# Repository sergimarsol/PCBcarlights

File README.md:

# PCB Car Lights

## Overview

PCB Car Lights is a project focused on the design and implementation of a printed circuit board (PCB) for controlling the lights of a car. This project provides the schematic and layout for the electronic components needed to efficiently manage car lighting systems.

## Table of Contents

1. [Introduction](#introduction)
2. [Getting Started](#getting-started)
3. [Schematic and Layout](#schematic-and-layout)
4. [Components](#components)
5. [Presentation](#presentation)
6. [Contributing](#contributing)

## Introduction

Modern cars rely on sophisticated lighting systems for safety and aesthetics. The PCB Car Lights project aims to streamline the control of car lights, providing a compact and efficient solution through a custom-designed PCB.

## Getting Started

To get started with the PCB Car Lights project, follow these steps:

1. **Clone the Repository:**
   ```bash
   git clone https://github.com/your-username/PCBcarlights.git
   ```

2. **Explore the Documentation:**
   Review the documentation files, including the README, to understand the project structure and requirements.

3. **Set Up Development Environment:**
   Ensure you have the necessary tools and software installed for PCB design. Refer to the documentation for specific requirements.

4. **Modify Design:**
   Customize the PCB design according to your car's lighting specifications, making any necessary adjustments to the schematic and layout.

5. **Testing:**
   Before manufacturing the PCB, simulate and test the design using appropriate tools to ensure functionality.

## Schematic and Layout

The schematic diagram provides an overview of the electronic components and their connections and the PCB layout file defines the physical arrangement of components on the board. Open both files using [Kicad] to view the schematic and the layout of the implemented PCB. Screenshots of both files and of the block diagram are also provided:

- [View Block diagram](./imgs/block_diagram.PNG)
- [View Schematic](./imgs/SCH_image.PNG)
- [View PCB](./imgs/PCB_image.PNG)

All of these can be observed in the provided presentation.

## Components

To view the components refer to the .xlsx file containing them along with their budget.

- [View components and budget](./Components_budget.xlsx)

The most relevant components can be found in the provided presentation

## Presentation

Included in this repository is a PDF presentation (`PCBcarlights_Presentation.pdf`) that provides a comprehensive overview of the project. The presentation covers background, design methodology, key features, and potential applications of the PCB Car Lights project.

## Contributing

If you have any questions or feedback, feel free to reach out to me.

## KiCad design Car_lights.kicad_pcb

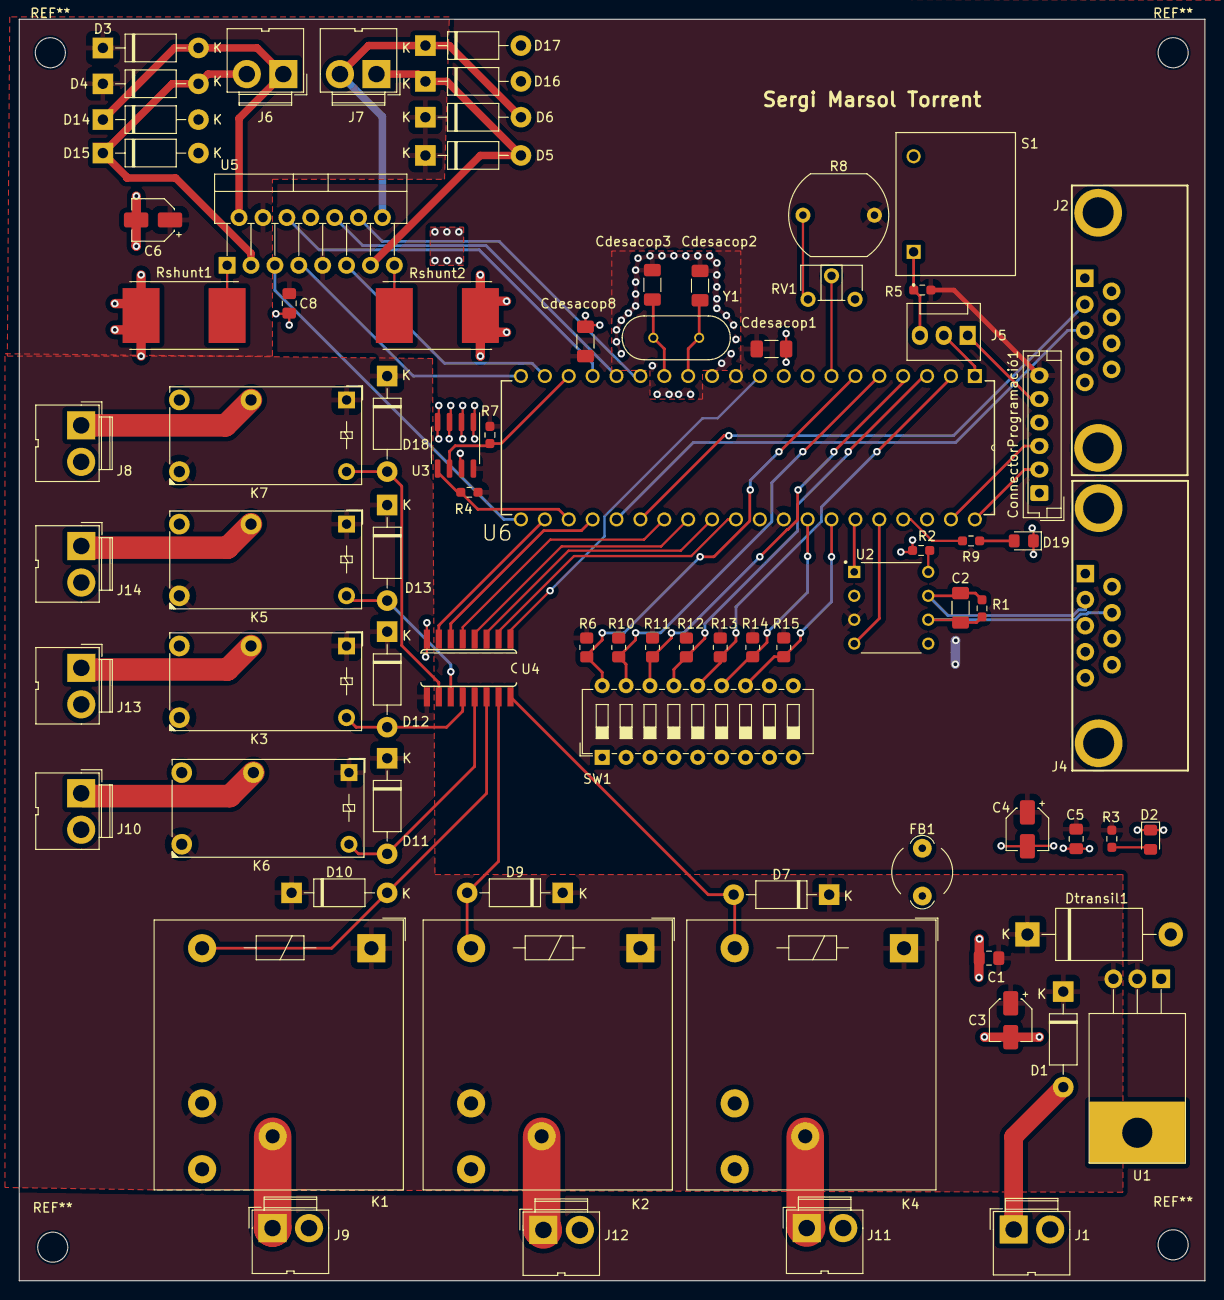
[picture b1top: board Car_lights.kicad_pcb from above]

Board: 2 copper layers, 126.1 x 134.1 mm, 80 parts (1 on the bottom side), 66 nets.

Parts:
C1, C5, C8: 100n; C_0805_2012Metric_Pad1.18x1.45mm_HandSolder
C2: 100p; C_1206_3216Metric_Pad1.33x1.80mm_HandSolder
C3, C4: 1u; CP_Elec_4x5.4
C6: 220n; CP_Elec_4x5.4
C7: 100n; C_1206_3216Metric_Pad1.33x1.80mm_HandSolder
Cdesacop1, Cdesacop8: 100n; C_1206_3216Metric_Pad1.33x1.80mm_HandSolder
Cdesacop2, Cdesacop3: 100p; C_1206_3216Metric_Pad1.33x1.80mm_HandSolder
ConnectorProgramació1: Conn_01x06; JST_EH_B6B-EH-A_1x06_P2.50mm_Vertical
D1, D7, D9, D10, D11, D12, D13, D18: 1N4002; D_DO-41_SOD81_P10.16mm_Horizontal
D2, D19: LED; LED_0805_2012Metric_Pad1.15x1.40mm_HandSolder
D3, D4, D5, D6, D14, D15, D16, D17: 1N4007; D_DO-41_SOD81_P10.16mm_Horizontal
Dtransil1: 1.5KExxA; D_DO-201AE_P15.24mm_Horizontal
FB1: FerriteBead; LairdTech_28C0236-0JW-10
J1: Conn_bat; JWT_A3963_1x02_P3.96mm_Vertical
J2: DB9_ConnectorUSART; DB9
J4: DB9_ConnectorCAN; DB9
J5: Conn_01x03; FanPinHeader_1x03_P2.54mm_Vertical
J6: Conn_Motor1; JWT_A3963_1x02_P3.96mm_Vertical
J7: Conn_Motor2; JWT_A3963_1x02_P3.96mm_Vertical
J8: Conn_I.E; JWT_A3963_1x02_P3.96mm_Vertical
J9: Conn_Fre; JWT_A3963_1x02_P3.96mm_Vertical
J10: Conn_Cruce; JWT_A3963_1x02_P3.96mm_Vertical
J11: Conn_Largas; JWT_A3963_1x02_P3.96mm_Vertical
J12: Conn_Antiniebla; JWT_A3963_1x02_P3.96mm_Vertical
J13: Conn_Posicio; JWT_A3963_1x02_P3.96mm_Vertical
J14: Conn_I.D; JWT_A3963_1x02_P3.96mm_Vertical
K1, K2, K4: G5LE-14-CF_DC24; Relay_SPDT_Finder_40.11
K3, K5, K6, K7: G5NB-1A-DC24; Relay_SPDT_Finder_32.21-x000
R1: 100; R_0603_1608Metric_Pad0.98x0.95mm_HandSolder
R2, R3, R5, R9: 1k; R_0603_1608Metric_Pad0.98x0.95mm_HandSolder
R4, R7: 4.7k; R_0603_1608Metric_Pad0.98x0.95mm_HandSolder
R6, R10, R11, R12, R13, R14, R15: 22k; R_0805_2012Metric_Pad1.20x1.40mm_HandSolder
R8: LDR03; R_LDR_10x8.5mm_P7.6mm_Vertical
RV1: R_Potentiometer; Potentiometer_ACP_CA6-H2,5_Horizontal
Rshunt1, Rshunt2: 250; R_Shunt_Vishay_WSR2_WSR3
S1: A3AT-91L1-00R; SW_A3AT-91L1-00R
SW1: SW_DIP_x09; SW_DIP_SPSTx09_Slide_6.7x24.42mm_W7.62mm_P2.54mm_LowProfile
U1: LM1117S-5.0; TO-220-3_Horizontal_TabDown (P2)
U2: MCP2551-I/P; DIP787W46P254L927H533Q8
U3: 24C02C/P; SOIC-8_3.9x4.9mm_P1.27mm
U4: ULN2003; SO16
U5: L298N; TO-220-15_P2.54x2.54mm_StaggerOdd_Lead4.58mm_Vertical
U6: PIC18F458-I/P; DIP254P1524X483-40
Y1: HC-49; XTAL_HC49P488W43L1150T466H350

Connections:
/+motor1: D3.2 (A), D14.1 (K), J6.1, U5.2 (OUT1)
/+motor2: D5.2 (A), D16.1 (K), J7.1, U5.13 (OUT3)
/-motor1: D4.2 (A), D15.1 (K), J6.2, U5.3 (OUT2)
/-motor2: D6.2 (A), D17.1 (K), J7.2, U5.14 (OUT4)
/CAN+: C2.1, J4.2, R1.1, U2.7 (CANH)
/CAN-: C2.2, J4.7, R1.2, U2.6 (CANL)
/CANRX: U2.4 (RXD), U6.36 (RB3/CANRX)
/CANTX: U2.1 (TXD), U6.35 (RB2/CANTX/INT2)
/Corriente3A_1: J10.1, K6.11
/Corriente3A_2: J13.1, K3.11
/Corriente3A_3: J14.1, K5.11
/Corriente3A_4: J8.1, K7.11
/Corriente8A_1: J11.1, K4.11
/Corriente8A_2: J12.1, K2.11
/Corriente8A_3: J9.1, K1.11
/MCLR: J5.2, U6.1 (~MCLR/VPP)
/PGC: ConnectorProgramació1.3, U6.39 (RB6/PGC)
/PGD: ConnectorProgramació1.2, U6.40 (RB7/PGD)
/PROG.MCLR: ConnectorProgramació1.5, J5.1
/Reset: J5.3, R5.2, S1.1
/led programació: D19.2 (A), R9.1
ADC: RV1.2, U6.7 (RA5/AN4/~SS/LVDIN)
CLK0: Cdesacop3.2, U6.14 (OSC2/CLKO/RA6), Y1.1
CLK1: Cdesacop2.1, U6.13 (OSC1/CLKI), Y1.2 (CRYSTAL_2)
ENA: U5.6 (EnA), U6.17 (RC2/CCP1)
ENB: U5.11 (EnB), U6.19 (RD0/PSP0/C1IN+)
GND: C4.2, C5.2, C7.2, C8.1, Cdesacop1.2, Cdesacop2.2, Cdesacop3.1, Cdesacop8.2, ConnectorProgramació1.1, D2.1 (K), D19.1 (K), FB1.2, J2.5, J4.3, R2.1, RV1.3, S1.2, SW1.1, SW1.2, SW1.3, SW1.4, SW1.5, SW1.6, SW1.7, U2.2 (VSS), U3.1 (E0), U3.2 (E1), U3.3 (E2), U3.4 (VSS), U3.7 (~WC), U4.8 (GND), U5.8 (GND), U6.12 (VSS_2), U6.31 (VSS)
GNDPWR: C1.2, C3.2, C6.2, D14.2 (A), D15.2 (A), D16.2 (A), D17.2 (A), Dtransil1.2 (A2), FB1.1, J1.2, J8.2, J9.2, J10.2, J11.2, J12.2, J13.2, J14.2, K1.14, K2.14, K3.14, K4.14, K5.14, K6.14, K7.14, Rshunt1.2, Rshunt2.2, U1.1 (GND)
I1: U4.1 (I1), U6.10 (RE2/AN7/~CS/C2OUT)
I2: U4.2 (I2), U6.30 (RD7/PSP7/P1D)
I3: U4.3 (I3), U6.29 (RD6/PSP6/P1C)
I4: U4.4 (I4), U6.28 (RD5/PSP5/P1B)
I5: U4.5 (I5), U6.27 (RD4/PSP4/ECCP1/P1A)
I6: U4.6 (I6), U6.24 (RC5/SDO)
I7: U4.7 (I7), U6.22 (RD3/PSP3/C2IN-)
IN1: U5.5 (IN1), U6.21 (RD2/PSP2/C2IN+)
IN2: U5.7 (IN2), U6.20 (RD1/PSP1/C1IN-)
IN3: U5.10 (IN3), U6.16 (RC1/T1OSI)
IN4: U5.12 (IN4), U6.15 (RC0/T1OSO/T1CK1)
unnamed: D2.2 (A), R3.2
unnamed: R8.1, RV1.1
unnamed: R2.2, U2.8 (RS)
unnamed: Rshunt1.1, U5.1 (SENSE_A)
unnamed: Rshunt2.1, U5.15 (SENSE_B)
unnamed: R9.2, U6.37 (RB4)
R1: D7.2 (A), K4.A2, U4.16 (O1)
R2: D9.2 (A), K2.A2, U4.15 (O2)
R3: D10.2 (A), K1.A2, U4.14 (O3)
R4: D11.2 (A), K6.A2, U4.13 (O4)
R5: D12.2 (A), K3.A2, U4.12 (O5)
R6: D13.2 (A), K5.A2, U4.11 (O6)
R7: D18.2 (A), K7.A2, U4.10 (O7)
RA0: R6.2, SW1.18, U6.6 (RA4/T0CKI)
RA1: R10.2, SW1.17, U6.5 (RA3/AN3/VREF+)
RA2: R11.2, SW1.16, U6.4 (RA2/AN2/VREF-)
RA3: R12.2, SW1.15, U6.3 (RA1/AN1)
RA4: R13.2, SW1.14, U6.2 (RA0/AN0/CVREF)
RB0: R15.2, SW1.12, U6.34 (RB1/INT1)
RB1: R14.2, SW1.13, U6.33 (RB0/INT0)
RX: J2.2, U6.26 (RC7/RX/DT)
SCL: R7.2, U3.6 (SCL), U6.18 (RC3/SCK/SCL)
SDA: R4.2, U3.5 (SDA), U6.23 (RC4/SDI/SDA)
TX: J2.3, U6.25 (RC6/TX/CK)
VBAT: D1.2 (A), J1.1
VBAT-PROT: C1.1, C3.1, C6.1, D1.1 (K), D3.1 (K), D4.1 (K), D5.1 (K), D6.1 (K), D7.1 (K), D9.1 (K), D10.1 (K), D11.1 (K), D12.1 (K), D13.1 (K), D18.1 (K), Dtransil1.1 (A1), K1.12, K1.A1, K2.12, K2.A1, K3.12, K3.A1, K4.A1, K5.12, K5.A1, K6.12, K6.A1, K7.12, K7.A1, U1.3 (VI), U4.9 (COM), U5.4 (Vs)
VCC: C4.1, C5.1, C7.1, C8.2, Cdesacop1.1, Cdesacop8.1, ConnectorProgramació1.6, R3.1, R4.1, R5.1, R6.1, R7.1, R8.2, R10.1, R11.1, R12.1, R13.1, R14.1, R15.1, U1.2 (VO), U2.3 (VDD), U3.8 (VCC), U5.9 (Vss), U6.11 (VDD), U6.32 (VDD_2)

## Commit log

2024-01-22 Create a
